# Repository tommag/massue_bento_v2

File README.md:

massue_bento_v2
===============

KiCad PCB for Bento juggling club

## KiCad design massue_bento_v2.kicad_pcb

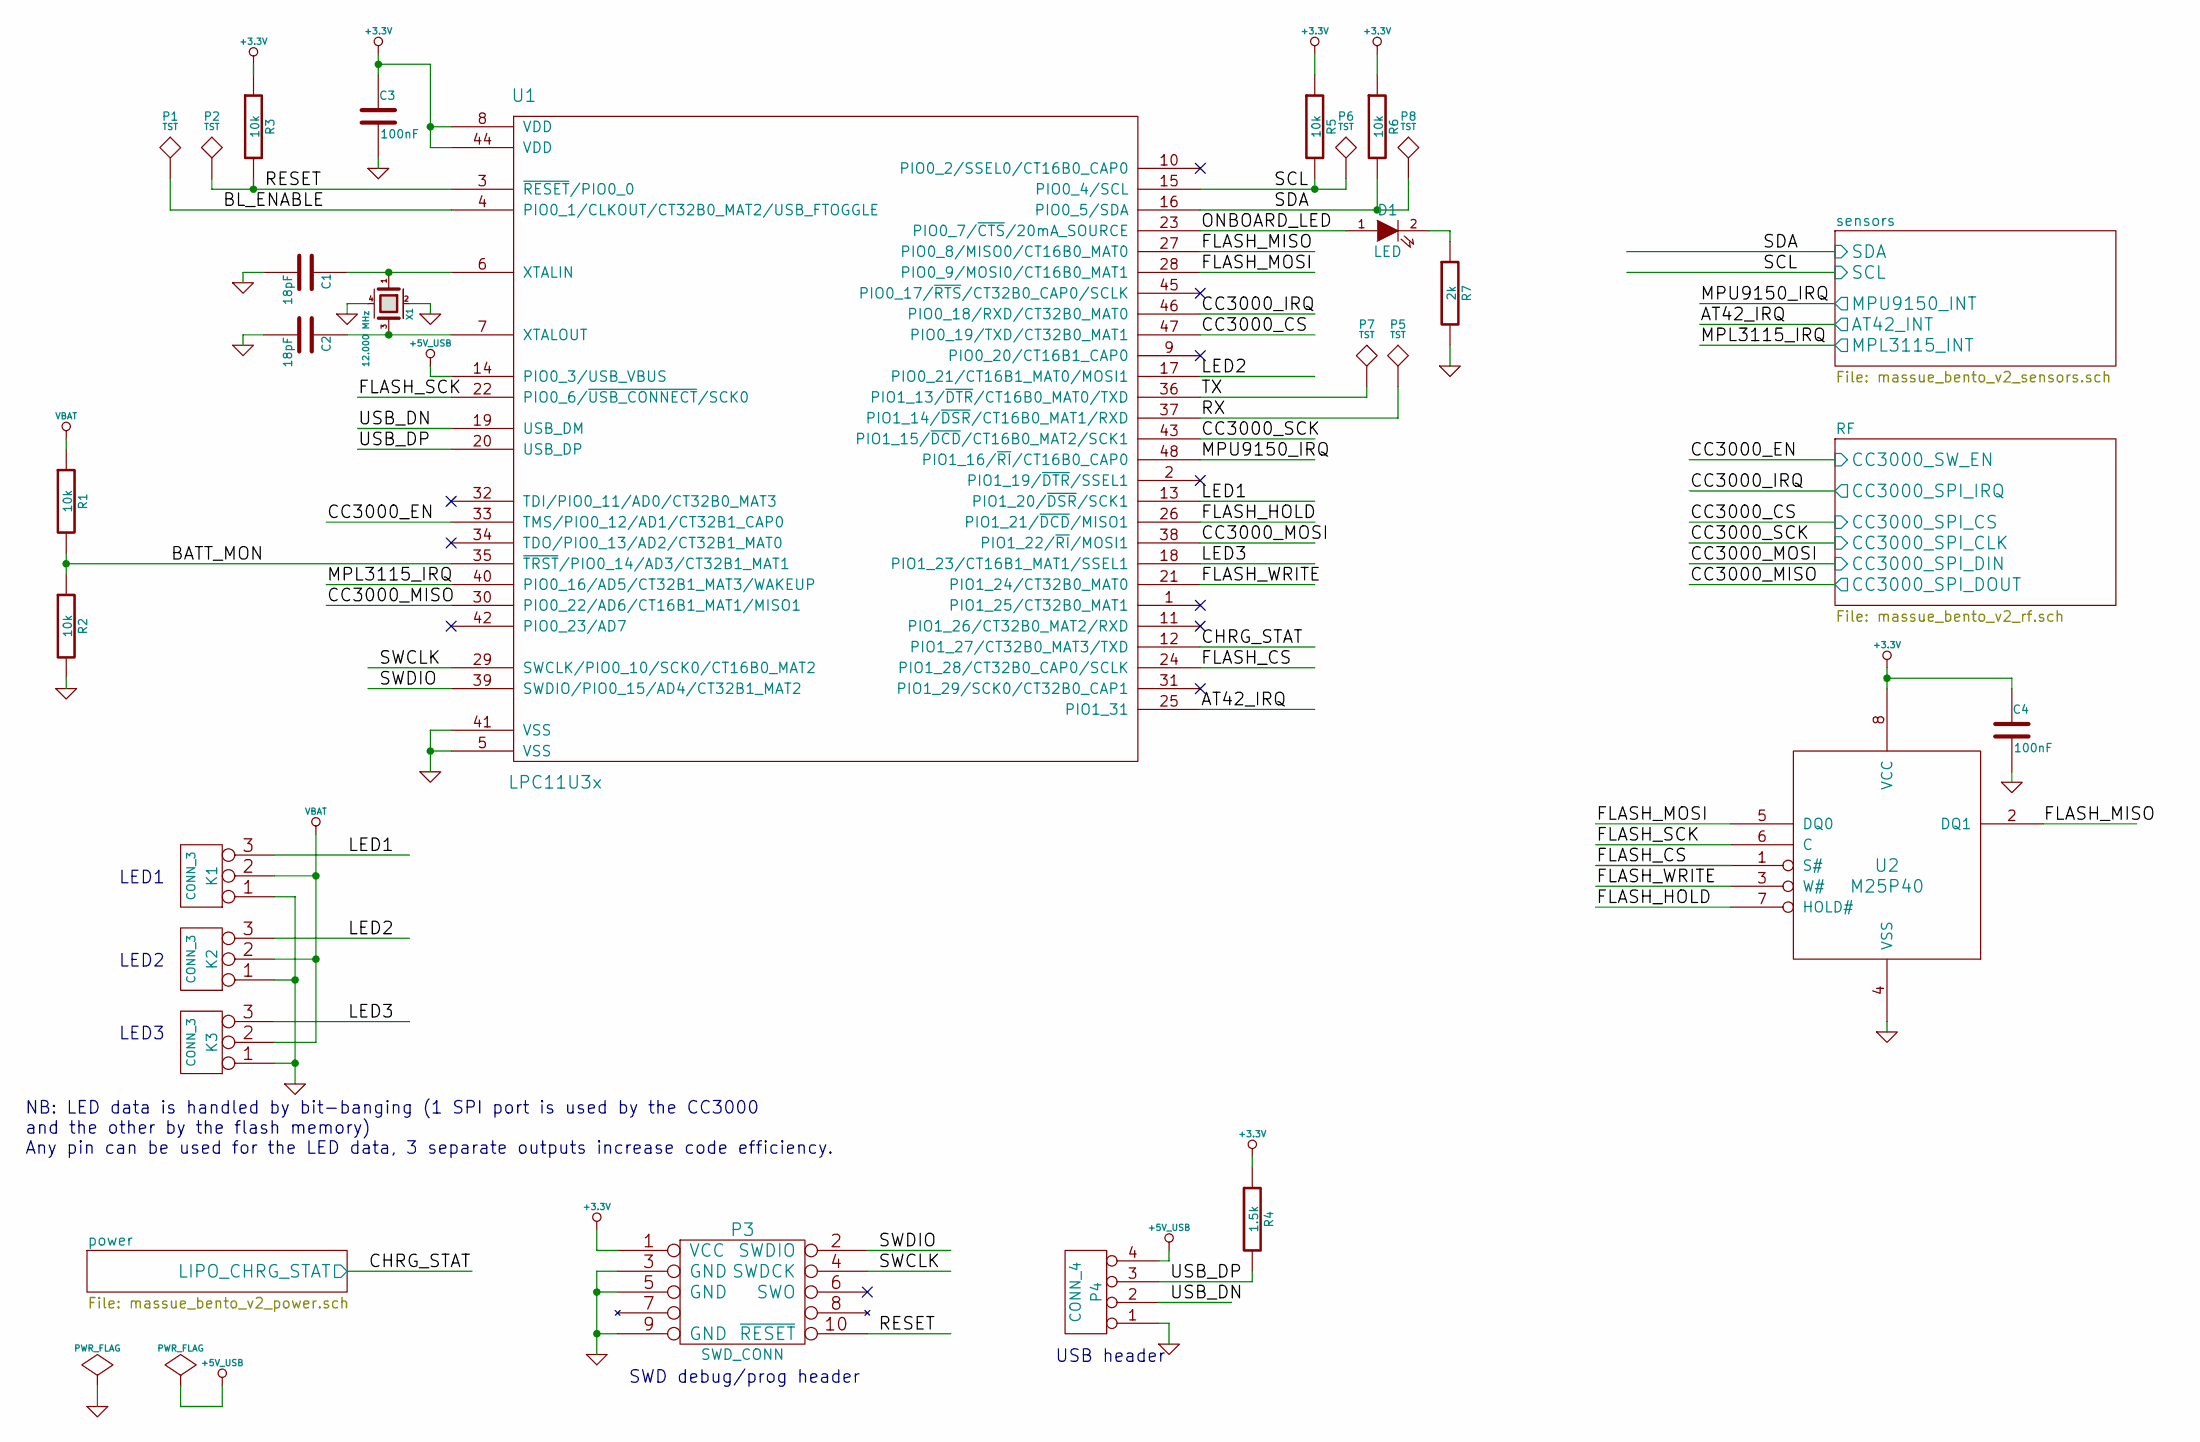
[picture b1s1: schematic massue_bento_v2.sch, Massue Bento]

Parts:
C1, C2: 18pF
C3, C4: 100nF
D1: LED
K1, K2, K3: CONN_3
P1, P2, P5, P6, P7, P8: TST
P3: SWD_CONN
P4: CONN_4
R1, R2, R3, R5, R6: 10k
R4: 1.5k
R7: 2k
U1: LPC11U3x
U2: M25P40
X1: 12.000 MHz

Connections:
+3.3V: C3.1, C4.1, P3.1 (VCC), R3.1, R4.1, R5.1, R6.1, U1.8 (VDD), U1.44 (VDD), U2.8 (VCC); also elsewhere on the board
+5V_USB: P4.4, U1.14 (PIO0_3/USB_VBUS); also elsewhere on the board
/BATT_MON: R1.2, R2.1, U1.35 (~TRST~/PIO0_14/AD3/CT32B1_MAT1)
/BL_ENABLE: P1.1, U1.4 (PIO0_1/CLKOUT/CT32B0_MAT2/USB_FTOGGLE)
/FLASH_CS: U1.24 (PIO1_28/CT32B0_CAP0/SCLK), U2.1 (S#)
/FLASH_HOLD: U1.26 (PIO1_21/~DCD~/MISO1), U2.7 (HOLD#)
/FLASH_MISO: U1.27 (PIO0_8/MISO0/CT16B0_MAT0), U2.2 (DQ1)
/FLASH_MOSI: U1.28 (PIO0_9/MOSI0/CT16B0_MAT1), U2.5 (DQ0)
/FLASH_SCK: U1.22 (PIO0_6/~USB_CONNECT~/SCK0), U2.6 (C)
/FLASH_WRITE: U1.21 (PIO1_24/CT32B0_MAT0), U2.3 (W#)
/LED1: K1.3, U1.13 (PIO1_20/~DSR~/SCK1)
/LED2: K2.3, U1.17 (PIO0_21/CT16B1_MAT0/MOSI1)
/LED3: K3.3, U1.18 (PIO1_23/CT16B1_MAT1/SSEL1)
/ONBOARD_LED: D1.1 (A), U1.23 (PIO0_7/~CTS~/20mA_SOURCE)
/RESET: P2.1, P3.10 (~RESET), R3.2, U1.3 (~RESET~/PIO0_0)
/RF/CC3000_SPI_CLK: U1.43 (PIO1_15/~DCD~/CT16B0_MAT2/SCK1); also elsewhere on the board
/RF/CC3000_SPI_CS: U1.47 (PIO0_19/TXD/CT32B0_MAT1); also elsewhere on the board
/RF/CC3000_SPI_DIN: U1.38 (PIO1_22/~RI~/MOSI1); also elsewhere on the board
/RF/CC3000_SPI_DOUT: U1.30 (PIO0_22/AD6/CT16B1_MAT1/MISO1); also elsewhere on the board
/RF/CC3000_SPI_IRQ: U1.46 (PIO0_18/RXD/CT32B0_MAT0); also elsewhere on the board
/RF/CC3000_SW_EN: U1.33 (TMS/PIO0_12/AD1/CT32B1_CAP0); also elsewhere on the board
/RX: P5.1, U1.37 (PIO1_14/~DSR~/CT16B0_MAT1/RXD)
/SWCLK: P3.4 (SWDCK), U1.29 (SWCLK/PIO0_10/SCK0/CT16B0_MAT2)
/SWDIO: P3.2 (SWDIO), U1.39 (SWDIO/PIO0_15/AD4/CT32B1_MAT2)
/TX: P7.1, U1.36 (PIO1_13/~DTR~/CT16B0_MAT0/TXD)
/USB_DN: P4.2, U1.19 (USB_DM)
/USB_DP: P4.3, R4.2, U1.20 (USB_DP)
/power/LIPO_CHRG_STAT: U1.12 (PIO1_27/CT32B0_MAT3/TXD); also elsewhere on the board
/sensors/AT42_INT: U1.25 (PIO1_31); also elsewhere on the board
/sensors/MPL3115_INT: U1.40 (PIO0_16/AD5/CT32B1_MAT3/WAKEUP); also elsewhere on the board
/sensors/MPU9150_INT: U1.48 (PIO1_16/~RI~/CT16B0_CAP0); also elsewhere on the board
/sensors/SCL: P6.1, R5.2, U1.15 (PIO0_4/SCL); also elsewhere on the board
/sensors/SDA: P8.1, R6.2, U1.16 (PIO0_5/SDA); also elsewhere on the board
GND: C1.2, C2.2, C3.2, C4.2, K1.1, K2.1, K3.1, P3.3 (GND), P3.5 (GND), P3.9 (GND), P4.1, R2.2, R7.2, U1.5 (VSS), U1.41 (VSS), U2.4 (VSS), X1.2 (GND), X1.4 (GND); also elsewhere on the board
unnamed: C1.1, U1.6 (XTALIN), X1.1
unnamed: C2.1, U1.7 (XTALOUT), X1.3
unnamed: D1.2 (K), R7.1
VBAT: K1.2 (PM), K2.2 (PM), K3.2 (PM), R1.1; also elsewhere on the board

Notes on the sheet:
USB header
SWD debug/prog header
LED1
LED2
LED3
NB: LED data is handled by bit-banging (1 SPI port is used by the CC3000 and the other by the flash memory) Any pin can be used for the LED data, 3 separate outputs increase code efficiency.

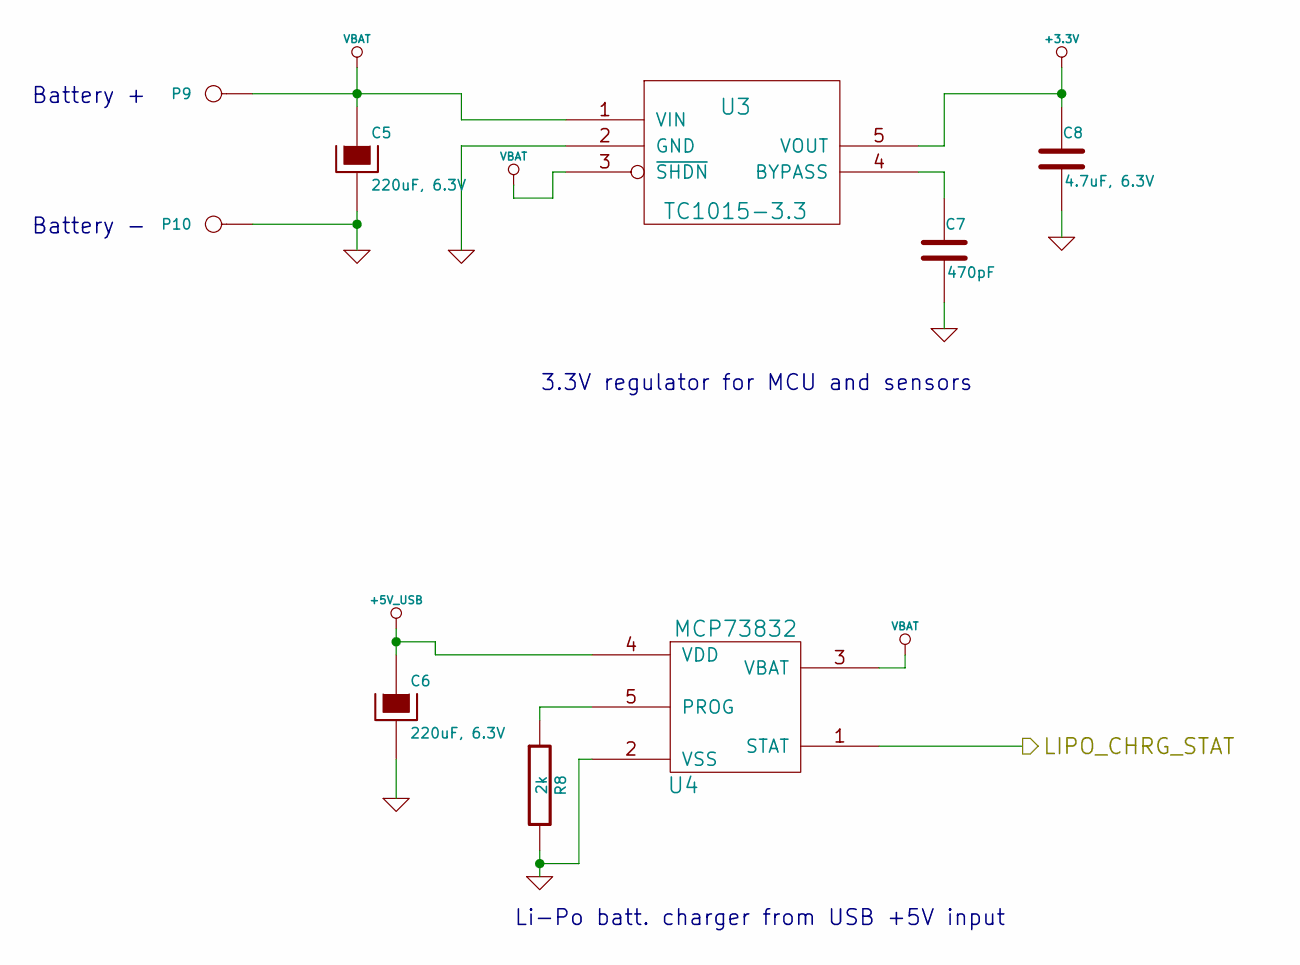
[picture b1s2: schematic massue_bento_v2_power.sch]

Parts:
C5, C6: 220uF, 6.3V
C7: 470pF
C8: 4.7uF, 6.3V
P9, P10: CONN_1
R8: 2k
U3: TC1015-3.3
U4: MCP73832

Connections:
+3.3V: C8.1, U3.5 (VOUT); also elsewhere on the board
+5V_USB: C6.1, U4.4 (VDD); also elsewhere on the board
/power/LIPO_CHRG_STAT: U4.1 (STAT); also elsewhere on the board
GND: C5.2, C6.2, C7.2, C8.2, P10.1, R8.2, U3.2 (GND), U4.2 (VSS); also elsewhere on the board
unnamed: C7.1, U3.4 (BYPASS)
unnamed: R8.1, U4.5 (PROG)
VBAT: C5.1, P9.1, U3.1 (VIN), U3.3 (~SHDN), U4.3 (VBAT); also elsewhere on the board

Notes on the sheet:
Battery +
Battery -
3.3V regulator for MCU and sensors
Li-Po batt. charger from USB +5V input

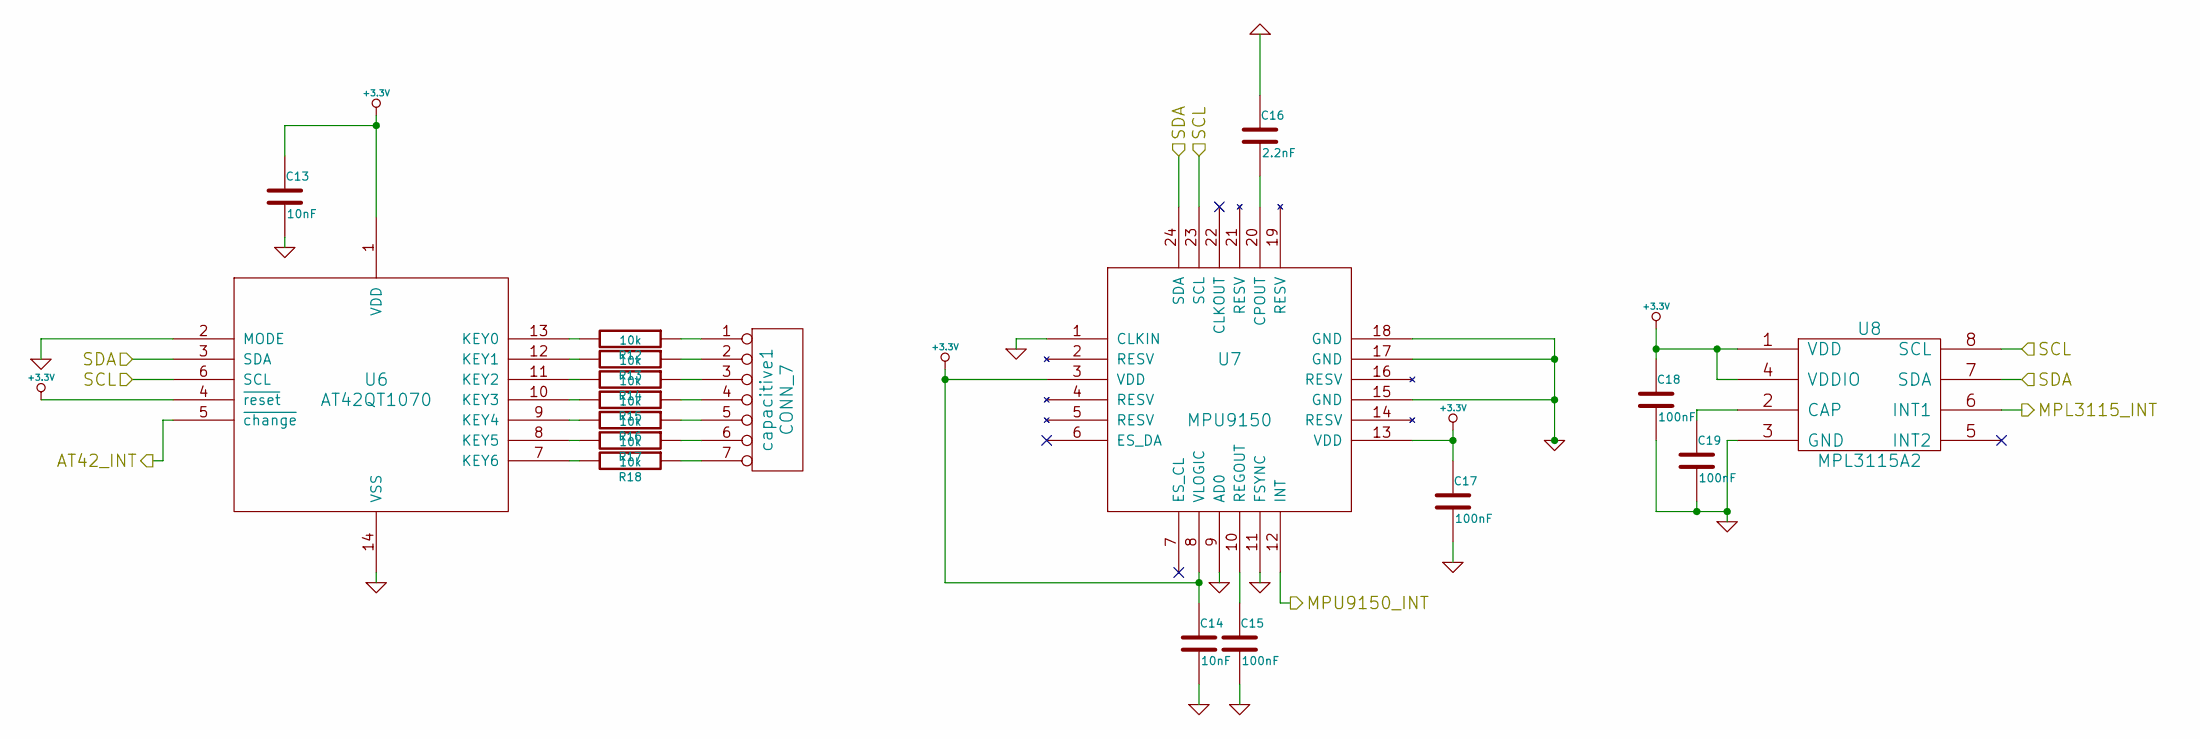
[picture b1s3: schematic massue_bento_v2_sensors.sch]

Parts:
C13, C14: 10nF
C15, C17, C18, C19: 100nF
C16: 2.2nF
R12, R13, R14, R15, R16, R17, R18: 10k
U6: AT42QT1070
U7: MPU9150
U8: MPL3115A2
capacitive1: CONN_7

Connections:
+3.3V: C13.1, C14.1, C17.1, C18.1, U6.1 (VDD), U6.4 (~reset), U7.3 (VDD), U7.8 (VLOGIC), U7.13 (VDD), U8.1 (VDD), U8.4 (VDDIO); also elsewhere on the board
/sensors/AT42_INT: U6.5 (~change); also elsewhere on the board
/sensors/MPL3115_INT: U8.6 (INT1); also elsewhere on the board
/sensors/MPU9150_INT: U7.12 (INT); also elsewhere on the board
/sensors/SCL: U6.6 (SCL), U7.23 (SCL), U8.8 (SCL); also elsewhere on the board
/sensors/SDA: U6.3 (SDA), U7.24 (SDA), U8.7 (SDA); also elsewhere on the board
GND: C13.2, C14.2, C15.2, C16.1, C17.2, C18.2, C19.2, U6.2 (MODE), U6.14 (VSS), U7.1 (CLKIN), U7.9 (AD0), U7.11 (FSYNC), U7.15 (GND), U7.17 (GND), U7.18 (GND), U8.3 (GND); also elsewhere on the board
unnamed: C15.1, U7.10 (REGOUT)
unnamed: C16.2, U7.20 (CPOUT)
unnamed: C19.1, U8.2 (CAP)
unnamed: R12.1, capacitive1.1
unnamed: R12.2, U6.13 (KEY0)
unnamed: R13.1, capacitive1.2
unnamed: R13.2, U6.12 (KEY1)
unnamed: R14.1, capacitive1.3
unnamed: R14.2, U6.11 (KEY2)
unnamed: R15.1, capacitive1.4
unnamed: R15.2, U6.10 (KEY3)
unnamed: R16.1, capacitive1.5
unnamed: R16.2, U6.9 (KEY4)
unnamed: R17.1, capacitive1.6
unnamed: R17.2, U6.8 (KEY5)
unnamed: R18.1, capacitive1.7
unnamed: R18.2, U6.7 (KEY6)

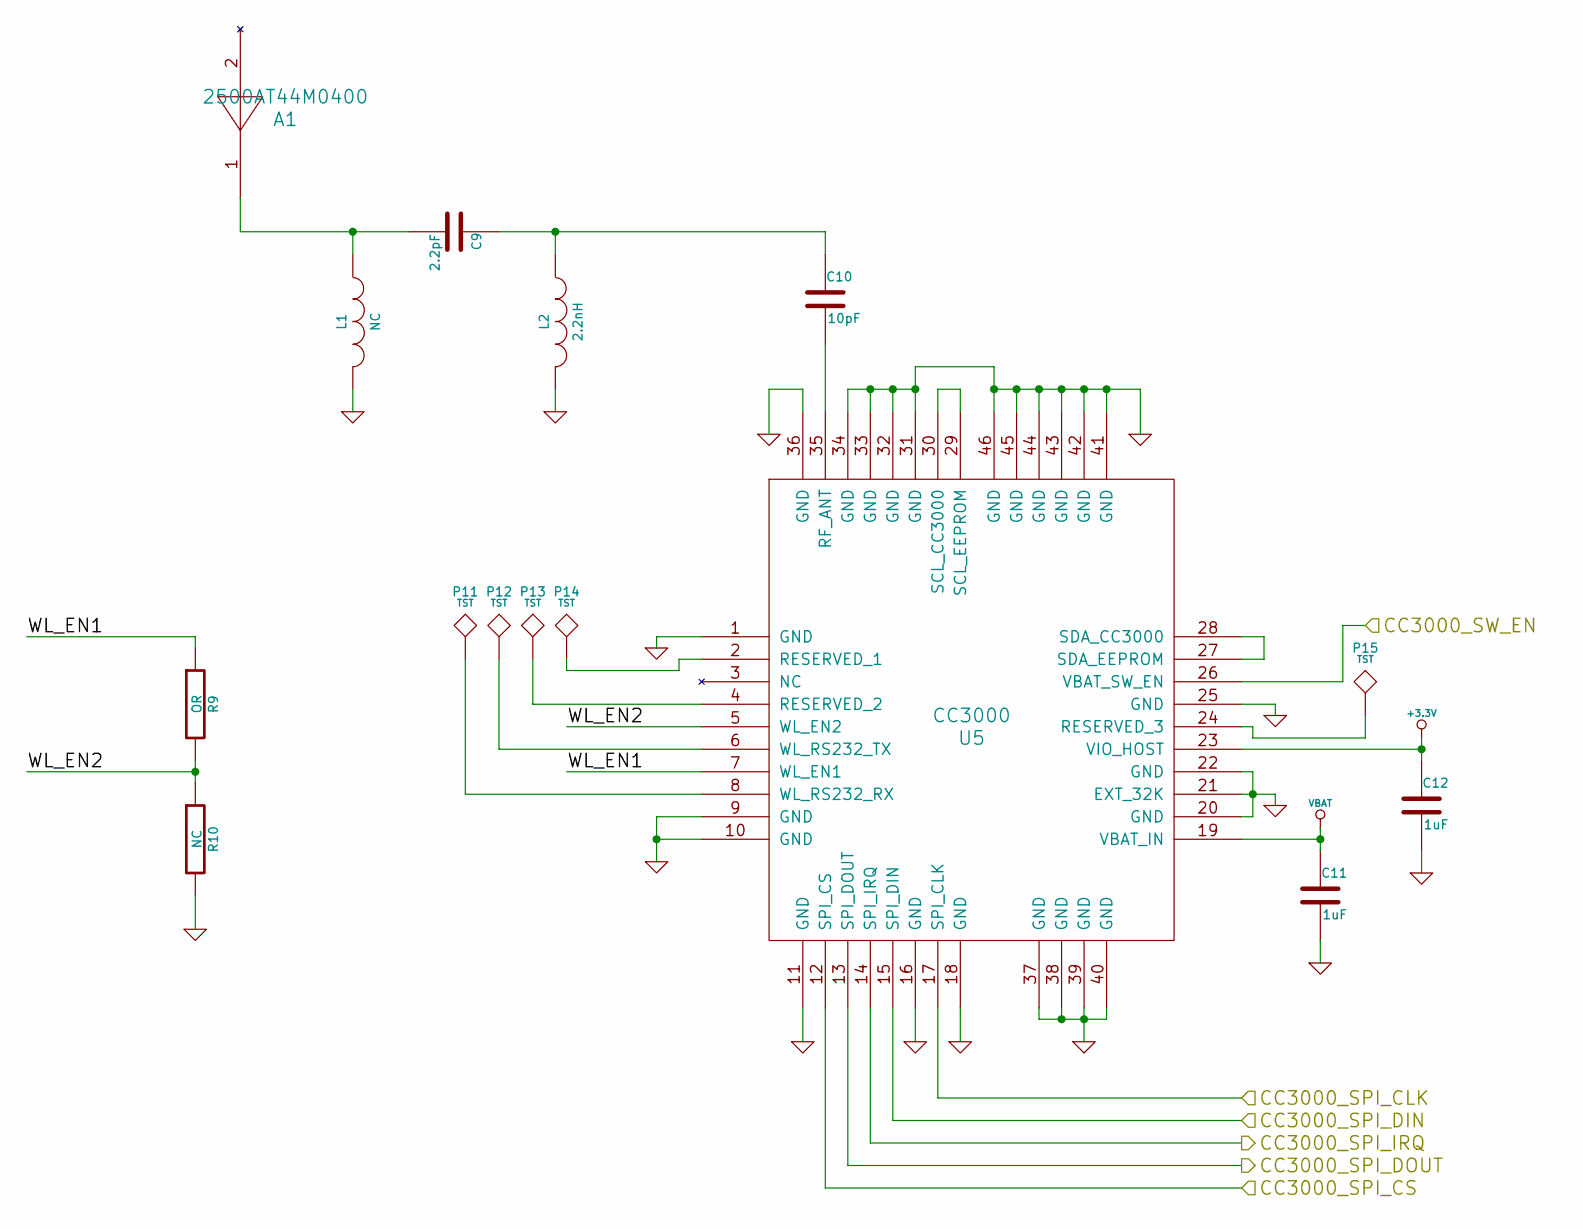
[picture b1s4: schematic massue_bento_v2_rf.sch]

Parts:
A1: 2500AT44M0400
C9: 2.2pF
C10: 10pF
C11, C12: 1uF
L1: NC
L2: 2.2nH
P11, P12, P13, P14, P15: TST
R9: OR
R10: NC
U5: CC3000

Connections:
+3.3V: C12.1, U5.23 (VIO_HOST); also elsewhere on the board
/RF/CC3000_SPI_CLK: U5.17 (SPI_CLK); also elsewhere on the board
/RF/CC3000_SPI_CS: U5.12 (SPI_CS); also elsewhere on the board
/RF/CC3000_SPI_DIN: U5.15 (SPI_DIN); also elsewhere on the board
/RF/CC3000_SPI_DOUT: U5.13 (SPI_DOUT); also elsewhere on the board
/RF/CC3000_SPI_IRQ: U5.14 (SPI_IRQ); also elsewhere on the board
/RF/CC3000_SW_EN: U5.26 (VBAT_SW_EN); also elsewhere on the board
/RF/WL_EN1: R9.1, U5.7 (WL_EN1)
/RF/WL_EN2: R9.2, R10.1, U5.5 (WL_EN2)
GND: C11.2, C12.2, L1.2, L2.2, R10.2, U5.1 (GND), U5.9 (GND), U5.10 (GND), U5.11 (GND), U5.16 (GND), U5.18 (GND), U5.20 (GND), U5.21 (EXT_32K), U5.22 (GND), U5.25 (GND), U5.31 (GND), U5.32 (GND), U5.33 (GND), U5.34 (GND), U5.36 (GND), U5.37 (GND), U5.38 (GND), U5.39 (GND), U5.40 (GND), U5.41 (GND), U5.42 (GND), U5.43 (GND), U5.44 (GND), U5.45 (GND), U5.46 (GND); also elsewhere on the board
unnamed: A1.1, C9.2, L1.1
unnamed: C9.1, C10.1, L2.1
unnamed: C10.2, U5.35 (RF_ANT)
unnamed: P11.1, U5.8 (WL_RS232_RX)
unnamed: P12.1, U5.6 (WL_RS232_TX)
unnamed: P13.1, U5.4 (RESERVED_2)
unnamed: P14.1, U5.2 (RESERVED_1)
unnamed: P15.1, U5.24 (RESERVED_3)
unnamed: U5.27 (SDA_EEPROM), U5.28 (SDA_CC3000)
unnamed: U5.29 (SCL_EEPROM), U5.30 (SCL_CC3000)
VBAT: C11.1, U5.19 (VBAT_IN); also elsewhere on the board

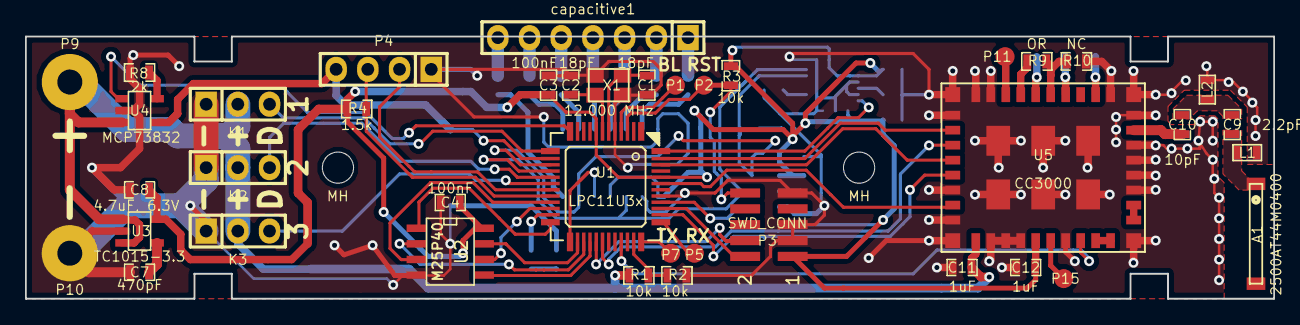
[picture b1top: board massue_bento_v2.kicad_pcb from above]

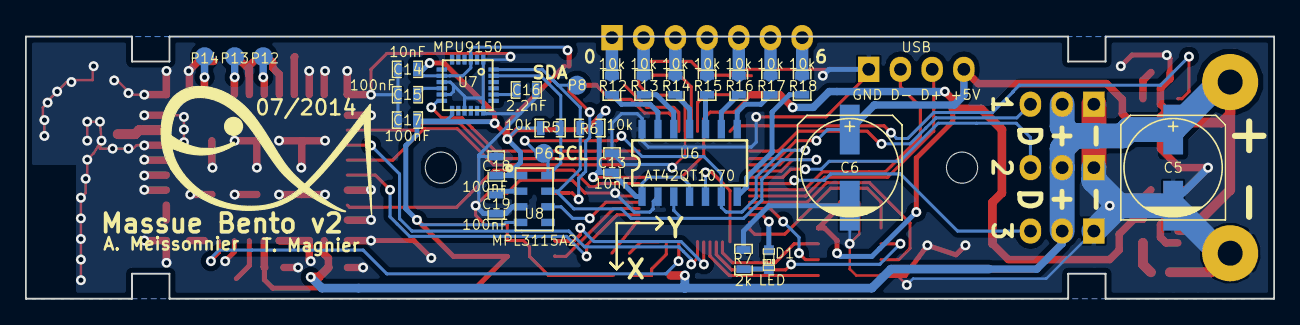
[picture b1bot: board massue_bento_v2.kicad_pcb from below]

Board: 2 copper layers, 100.0 x 21.0 mm, 70 parts (28 on the bottom side), 69 nets.

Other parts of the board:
MH: MountingHole_2-5mm_RevA_Date21Jun2010; MountingHole_2-5mm
MH#2: MountingHole_2-5mm_RevA_Date21Jun2010; MountingHole_2-5mm

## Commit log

2014-06-21 Added .gitignore file
2014-06-21 add empty schematic file
2014-06-21 New : sub sheets creation for team working :)
2014-06-21 Add: RF / CC3000 schematic section based upon reference design
2014-06-21 Fix: use battery voltage to power CC3000
2014-06-21 Add: power management schematic section
2014-06-21 Merge branch 'master' of https://github.com/tommag/massue_bento_v2
    Conflicts:
    massue_bento_v2_power.sch
    massue_bento_v2_rf.sch
2014-06-21 New: main MCU connections and Flash memory
2014-06-22 New: end of the MCU connections, SPI ports connections, battery monitor circuit and LED headers
2014-06-22 Fix: global annotation, fixed bugs to satisfy ERC
2014-06-22 New : AT42 sensor
2014-06-22 New : net list
2014-06-22 Fix : pull up for I2C and AT42INT connection
2014-06-25 New: association of footprints and components
2014-06-25 Clean: remove unnecessary pull-up resistor (integrated in MCU)
2014-06-25 Clean: replaced all test points by smaller version
2014-06-25 Clean: modified .gitignore to ignore PCB and lib backup files
2014-06-25 New: board outline and first raw component placement
2014-06-25 New: Setup design rules and trace widths
2014-06-26 Begin RF routing
2014-06-26 Clean: replaced all test points for SMD pads
2014-06-26 CC3000 and RF routing
2014-06-26 Fix: error in CC3000 component pinout
2014-06-27 New component placement
2014-06-27 New : Power routing
2014-06-28 Restore ground routing for CC3000
2014-06-28 Fix: LED strips are powered by VBAT and not 3.3V ; changed MCU pins to reflect component placement
2014-06-28 New: first routing for almost all signals
2014-06-29 Finished routing of signals, re-organization of power
2014-06-30 new : power ehencement
2014-07-01 New: first complete routing, no more unconnected nets
2014-07-03 Changed MS5607 altimeter for MPL3115A2
2014-07-03 Clean: additionnal ground vias, fixed USB differential signals length, add some labels
2014-07-03 Added version label and logo
2014-07-03 Add X/Y label for IMU axes
2014-07-04 Clean: same value for 100nF/0.1uf capacitors, re-organization of labels, add dimension labels
